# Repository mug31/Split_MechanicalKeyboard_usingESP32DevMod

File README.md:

# Split_MechanicalKeyboard_usingESP32DevMod
My journey building a wireless split keyboard from scratch using ESP32 Dev Module. Includes custom firmware for matrix scanning and layer management.
## 📝 To-Do List
- [x] Protoyping the keyboard using breadboard n pushbutton
- [x] Connecting left-right side
- [x] Implement debouncing logic.
- [ ] Add battery level monitoring over BLE.
- [x] making the PCB file
- [ ] Design 3D printable case.

*This is the prototype using breadboard-pushbutton, and it was using the matrix 4x5.*

## This is how the pcb looks like
i use KICAD to make this PCB, and for the footprint i use library from scotto keebs https://github.com/joe-scotto/scottokeebs/tree/main/Extras/ScottoKicad
| **Left side** | **Right side** |
|:---:|:---:|
|  |  |

| **The Plate** |
|:---:|
|  |
| *Plate for the switch* |

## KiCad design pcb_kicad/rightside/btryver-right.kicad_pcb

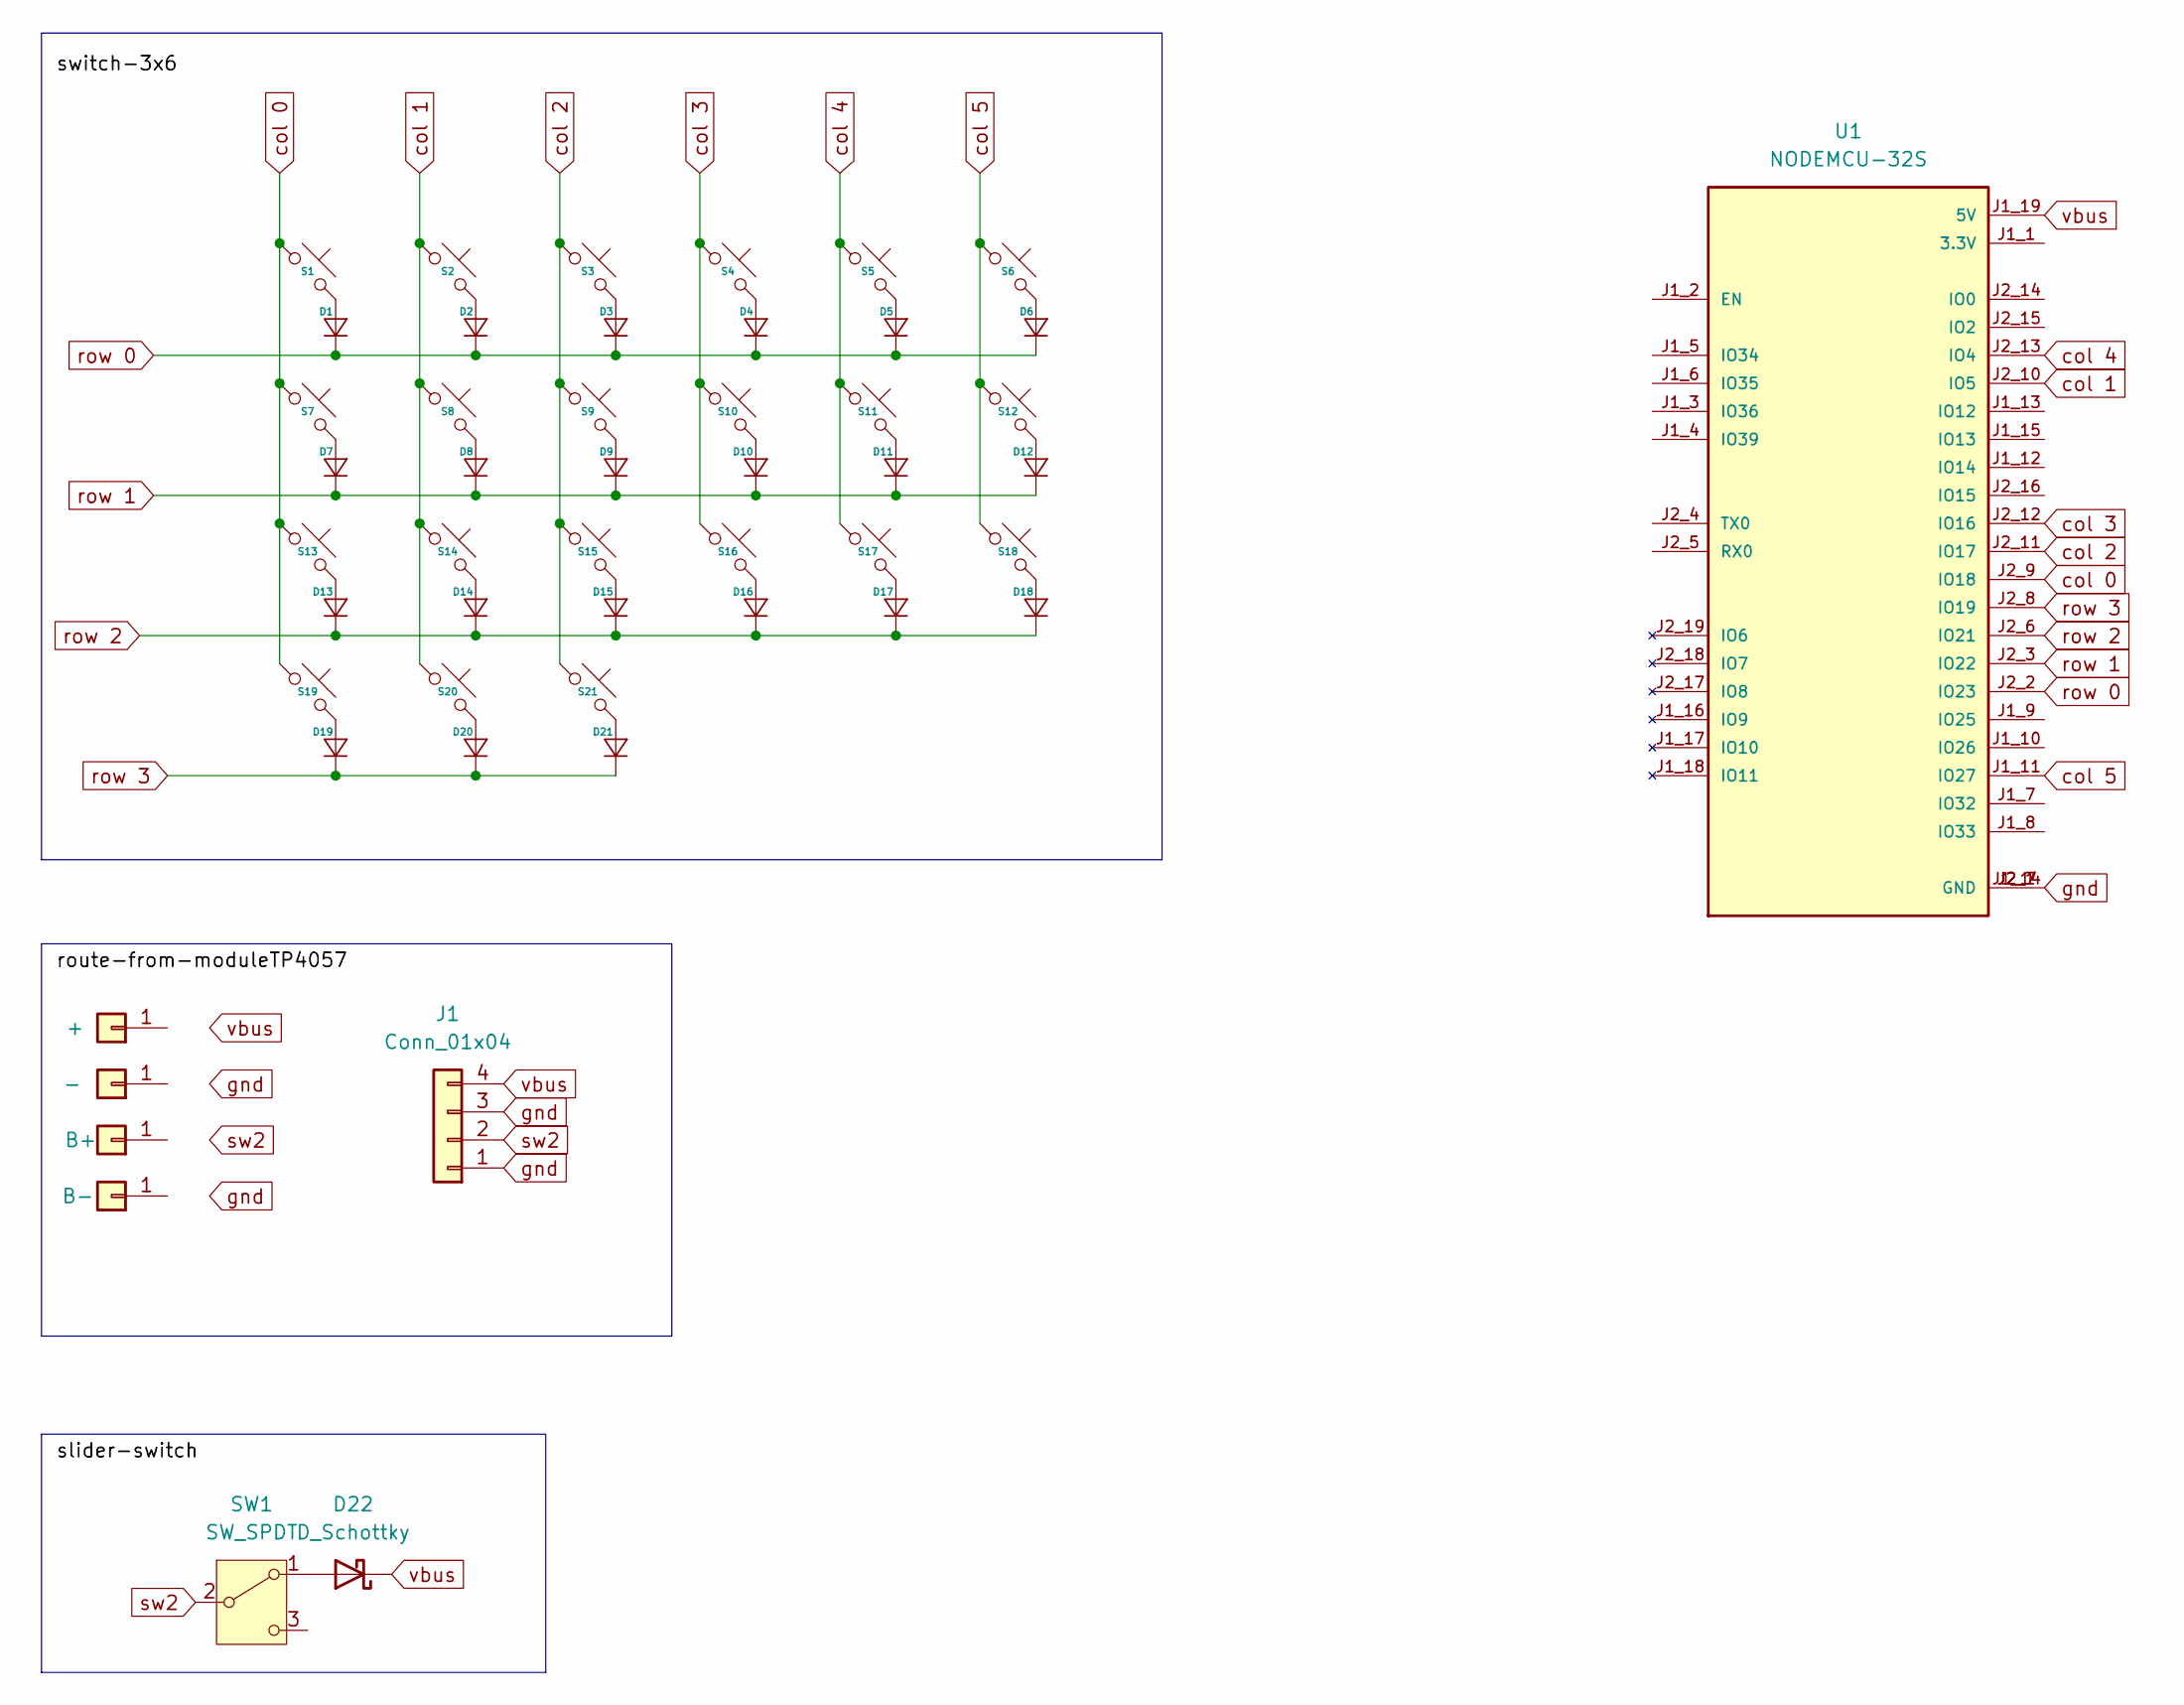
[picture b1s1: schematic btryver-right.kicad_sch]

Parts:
D1, D2, D3, D4, D5, D6, D7, D8, D9, D10, D11, D12, D13, D14, D15, D16, D17, D18, D19, D20, D21: Diode_SOD-123
D22: D_Schottky; D_SOD-123
J1: Conn_01x04; FanPinHeader_1x04_P2.54mm_Vertical
J3: B-; PinHeader_1x01_P2.54mm_Vertical
J5: -; PinHeader_1x01_P2.54mm_Vertical
J6: B+; PinHeader_1x01_P2.54mm_Vertical
J7: +; PinHeader_1x01_P2.54mm_Vertical
S1, S2, S3, S4, S5, S6, S7, S8, S9, S10, S11, S12, S13, S14, S15, S16, S17, S18, S19, S20, S21: Hotswap_MX_1.00u
SW1: SW_SPDT; SW_SPDT_PCM12
U1: NODEMCU-32S; MODULE_NODEMCU-32S; PARTREV V1

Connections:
unnamed: D1.2 (A), S1.2
unnamed: D2.2 (A), S2.2
unnamed: D3.2 (A), S3.2
unnamed: D4.2 (A), S4.2
unnamed: D5.2 (A), S5.2
unnamed: D6.2 (A), S6.2
unnamed: D7.2 (A), S7.2
unnamed: D8.2 (A), S8.2
unnamed: D9.2 (A), S9.2
unnamed: D10.2 (A), S10.2
unnamed: D11.2 (A), S11.2
unnamed: D12.2 (A), S12.2
unnamed: D13.2 (A), S13.2
unnamed: D14.2 (A), S14.2
unnamed: D15.2 (A), S15.2
unnamed: D16.2 (A), S16.2
unnamed: D17.2 (A), S17.2
unnamed: D18.2 (A), S18.2
unnamed: D19.2 (A), S19.2
unnamed: D20.2 (A), S20.2
unnamed: D21.2 (A), S21.2
unnamed: D22.2 (A), SW1.1 (A)
col 0: S1.1, S7.1, S13.1, S19.1, U1.J2_9 (IO18)
col 1: S2.1, S8.1, S14.1, S20.1, U1.J2_10 (IO5)
col 2: S3.1, S9.1, S15.1, S21.1, U1.J2_11 (IO17)
col 3: S4.1, S10.1, S16.1, U1.J2_12 (IO16)
col 4: S5.1, S11.1, S17.1, U1.J2_13 (IO4)
col 5: S6.1, S12.1, S18.1, U1.J1_11 (IO27)
gnd: J1.1, J1.3, U1.J1_14 (GND), U1.J2_1 (GND), U1.J2_7 (GND)
row 0: D1.1 (K), D2.1 (K), D3.1 (K), D4.1 (K), D5.1 (K), D6.1 (K), U1.J2_2 (IO23)
row 1: D7.1 (K), D8.1 (K), D9.1 (K), D10.1 (K), D11.1 (K), D12.1 (K), U1.J2_3 (IO22)
row 2: D13.1 (K), D14.1 (K), D15.1 (K), D16.1 (K), D17.1 (K), D18.1 (K), U1.J2_6 (IO21)
row 3: D19.1 (K), D20.1 (K), D21.1 (K), U1.J2_8 (IO19)
sw2: J1.2, SW1.2 (B)
vbus: D22.1 (K), J1.4, U1.J1_19 (5V)

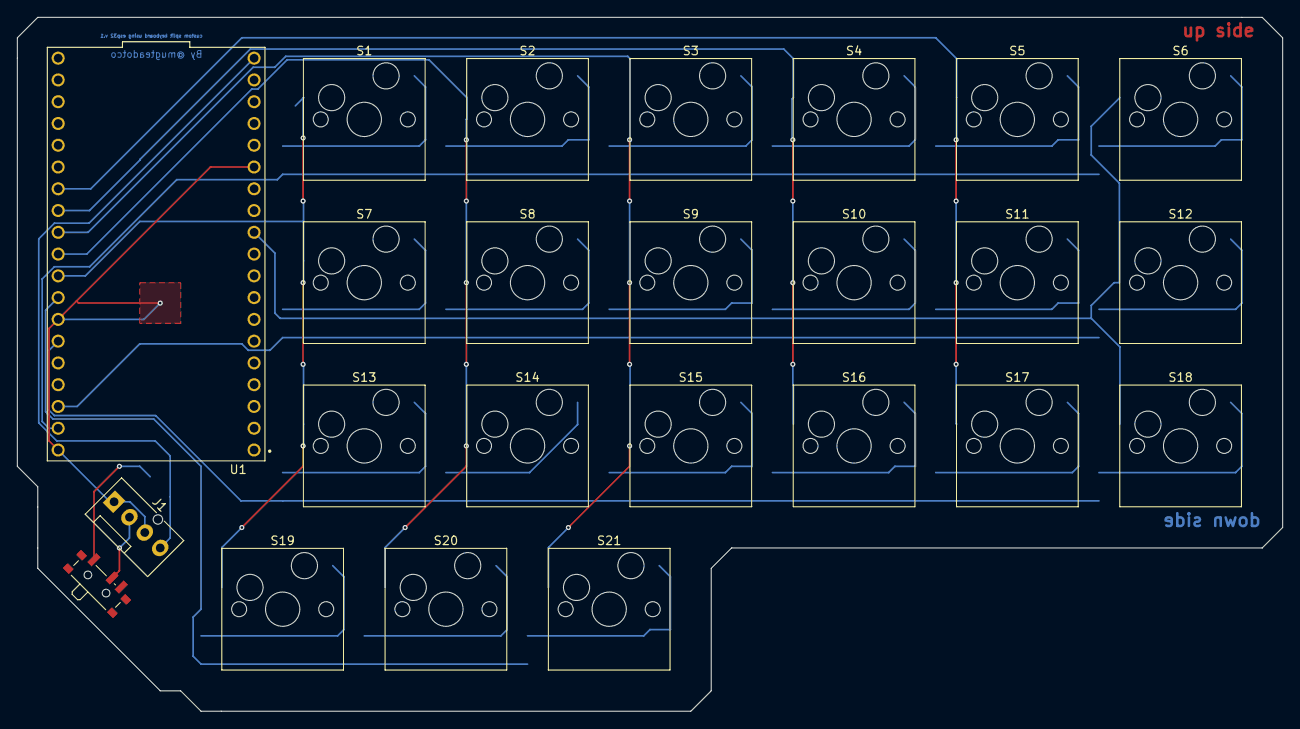
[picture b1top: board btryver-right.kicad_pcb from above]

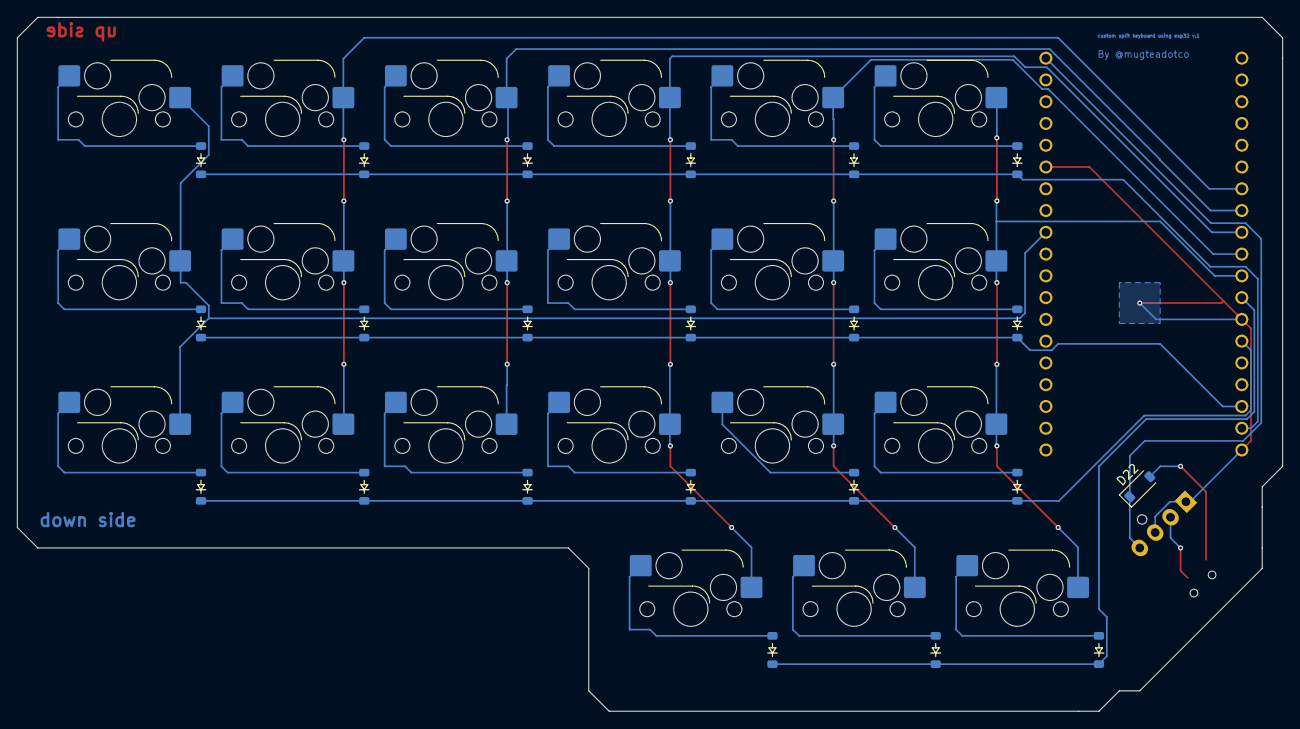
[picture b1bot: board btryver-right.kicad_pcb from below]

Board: 2 copper layers, 147.6 x 81.0 mm, 46 parts (22 on the bottom side), 35 nets.

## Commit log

2025-11-24 Add To-Do list for keyboard project
2025-11-24 Add files via upload
    this how the prototype look by using breadboard-pushbutton. And also the esp32 that i use
2025-11-24 Update README with prototype details
    Added a note about the prototype using a breadboard and pushbutton.
2025-11-24 Add firmware code to Prototyping folder
2025-11-24 Nambahin file PDF dokumentasi
2025-11-24 Remove author comment from testing_keyboard_2.ino
    Removed
2026-01-09 Update To-Do list with completed tasks
2026-01-17 Update README with completed PCB file task
2026-01-17 Update README with PCB images and prototype details
    Added images and descriptions of the PCB and prototype.
2026-01-17 Revise PCB section with KICAD info and images
    Updated PCB section with KICAD details and organized images in a table format.
2026-01-17 Create Pcb_kicad
2026-01-17 Create kicad_pcb
